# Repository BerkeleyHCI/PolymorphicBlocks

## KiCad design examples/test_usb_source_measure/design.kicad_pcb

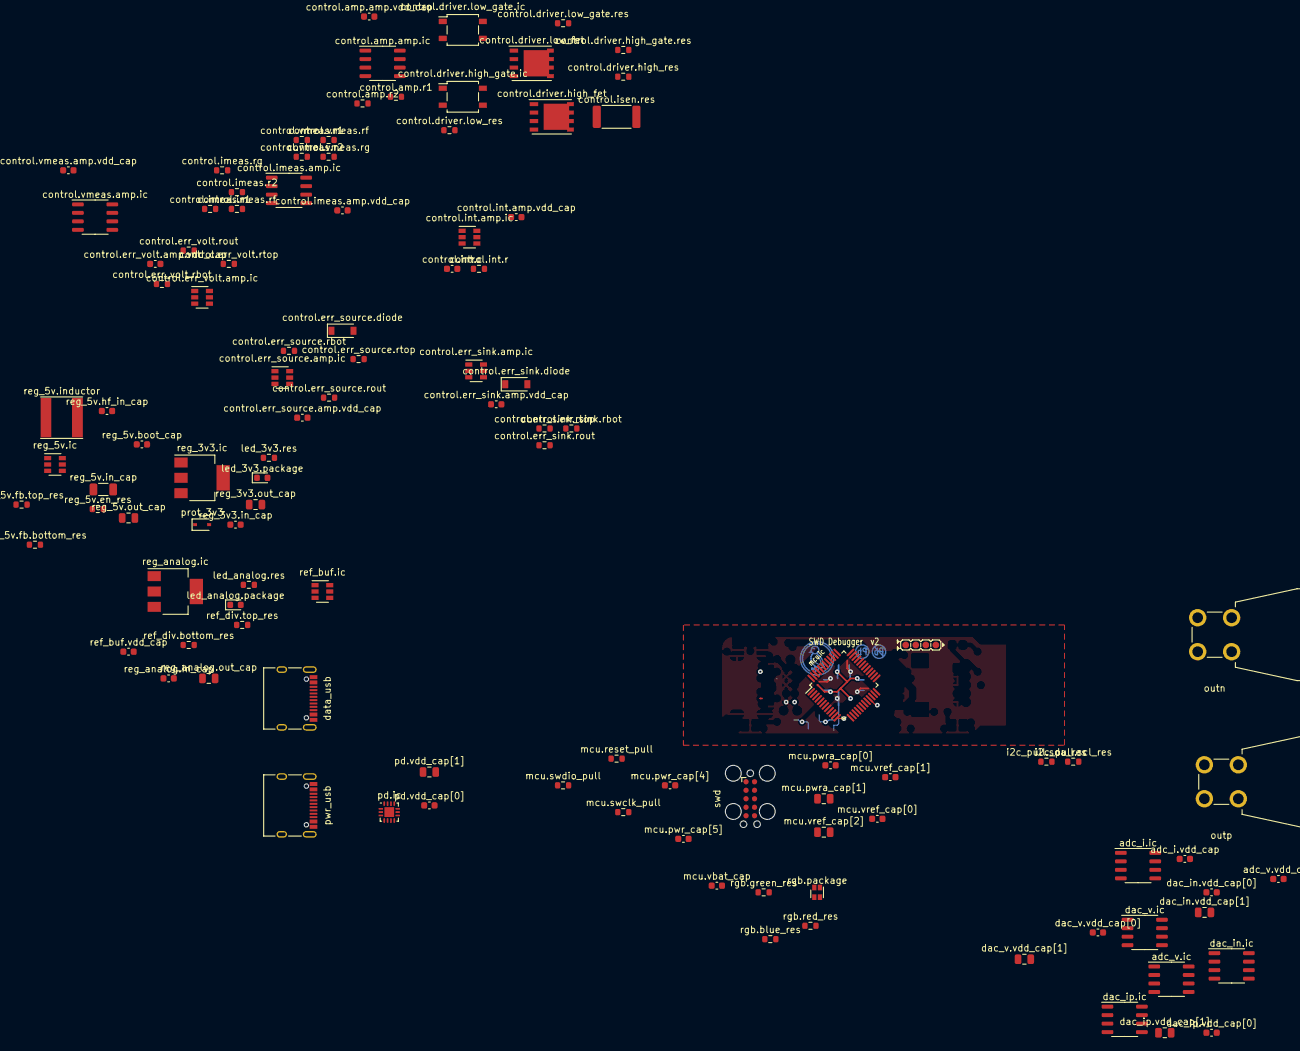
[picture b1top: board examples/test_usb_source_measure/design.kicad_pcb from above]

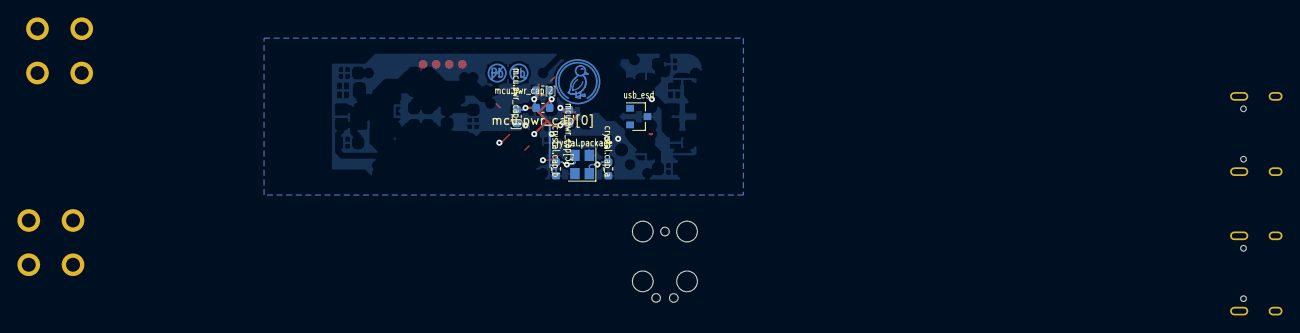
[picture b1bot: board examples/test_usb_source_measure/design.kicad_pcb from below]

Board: 4 copper layers, 120 parts (10 on the bottom side), 75 nets.

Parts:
adc_i.ic: MCP3201T-BI/SN (Microchip Technology); SO-8_3.9x4.9mm_P1.27mm
adc_i.vdd_cap: CL10A105KP8NNNC (Samsung Electro-Mechanics) - 1µF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; C_0603_1608Metric
adc_v.ic: MCP3201T-BI/SN (Microchip Technology); SO-8_3.9x4.9mm_P1.27mm
adc_v.vdd_cap: CL10A105KP8NNNC (Samsung Electro-Mechanics) - 1µF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; C_0603_1608Metric
control.amp.amp.ic, control.imeas.amp.ic, control.vmeas.amp.ic: OPA197IDR (Texas Instruments); SO-8_3.9x4.9mm_P1.27mm
control.amp.amp.vdd_cap, control.err_sink.amp.vdd_cap, control.err_source.amp.vdd_cap, control.err_volt.amp.vdd_cap, control.imeas.amp.vdd_cap, control.int.amp.vdd_cap, control.vmeas.amp.vdd_cap: CL10B104KB8NNNC (Samsung Electro-Mechanics) - 0.1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; C_0603_1608Metric
control.amp.r1: 39k, 1%, 0.1 W; R_0603_1608Metric
control.amp.r2: 2k, 1%, 0.1 W; R_0603_1608Metric
control.driver.high_fet: SIR172ADP-T1-GE3 (Vishay Siliconix) - Vds=30 V, I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; PowerPAK_SO-8_Single
control.driver.high_gate.ic, control.driver.low_gate.ic: G3VM-61GR2 (Omron Electronics); SO-4_4.4x4.3mm_P2.54mm
control.driver.high_gate.res, control.driver.low_gate.res: 220, 1%, 0.1 W; R_0603_1608Metric
control.driver.high_res, control.driver.low_res, control.err_sink.rout, control.err_source.rout, control.err_volt.rout, control.int.r: 4.7k, 1%, 0.1 W; R_0603_1608Metric
control.driver.low_fet: SQJ433EP-T1_GE3 (Vishay Siliconix) - Vds=30 V, Id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; PowerPAK_SO-8_Single
control.err_sink.amp.ic, control.err_source.amp.ic, control.err_volt.amp.ic, control.int.amp.ic: TLV9061SQDBVRQ1 (Texas Instruments); SOT-23-6
control.err_sink.diode, control.err_source.diode: DSS14UTR (SMC Diode Solutions) - Vr=40V, I=1A; D_SOD-123
control.err_sink.rbot, control.err_sink.rtop, control.err_source.rbot, control.err_source.rtop, control.err_volt.rbot, control.err_volt.rtop: 100k, 1%, 0.1 W; R_0603_1608Metric
control.imeas.r1, control.imeas.r2, control.imeas.rf, control.imeas.rg, control.vmeas.rf, control.vmeas.rg: 10k, 1%, 0.1 W; R_0603_1608Metric
control.int.c: CC0603GRNPO9BN102 (Yageo) - 1000pF, 50V; C_0603_1608Metric
control.isen.res: 100m, 1%, 1.0 W; R_2512_6332Metric
control.vmeas.r1, control.vmeas.r2: 220k, 1%, 0.1 W; R_0603_1608Metric
crystal.cap_a, crystal.cap_b: CL10C100JB8NNNC (Samsung Electro-Mechanics) - 10p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; C_0603_1608Metric
crystal.package: ABM8G-106-12.000MHZ-T (Abracon LLC) - 12MHz, 10pF; Oscillator_SMD_Abracon_ASE-4Pin_3.2x2.5mm
dac_in.ic: MCP4921-E/SN (Microchip Technology); SO-8_3.9x4.9mm_P1.27mm
dac_in.vdd_cap[0]: CL10B104KB8NNNC (Samsung Electro-Mechanics) - 0.1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; C_0603_1608Metric
dac_in.vdd_cap[1]: CL21A106KPFNNNE (Samsung Electro-Mechanics) - 10µ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; C_0805_2012Metric
dac_ip.ic: MCP4921-E/SN (Microchip Technology); SO-8_3.9x4.9mm_P1.27mm
dac_ip.vdd_cap[0]: CL10B104KB8NNNC (Samsung Electro-Mechanics) - 0.1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; C_0603_1608Metric
dac_ip.vdd_cap[1]: CL21A106KPFNNNE (Samsung Electro-Mechanics) - 10µ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; C_0805_2012Metric
dac_v.ic: MCP4921-E/SN (Microchip Technology); SO-8_3.9x4.9mm_P1.27mm
dac_v.vdd_cap[0]: CL10B104KB8NNNC (Samsung Electro-Mechanics) - 0.1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; C_0603_1608Metric
dac_v.vdd_cap[1]: CL21A106KPFNNNE (Samsung Electro-Mechanics) - 10µ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; C_0805_2012Metric
data_usb: COM-15111 (Sparkfun); USB_C_Receptacle_XKB_U262-16XN-4BVC11
duck: Duck; Symbol_Duckling
i2c_pull.scl_res, i2c_pull.sda_res: 4.7k, 1%, 0.1 W; R_0603_1608Metric
id: IdDots4; Indicator_IdDots_4
leadfree: LeadFree; Indicator_LeadFree
led_3v3.package: LED; LED_0603_1608Metric
led_3v3.res: 1k, 1%, 0.1 W; R_0603_1608Metric
led_analog.package: LED; LED_0603_1608Metric
led_analog.res: 1k, 1%, 0.1 W; R_0603_1608Metric
mcu.ic: LPC1549JBD48 (NXP); LQFP-48_7x7mm_P0.5mm
mcu.pwr_cap[0], mcu.pwr_cap[2], mcu.pwr_cap[4], mcu.pwra_cap[0], mcu.vbat_cap, mcu.vref_cap[0], mcu.vref_cap[1]: CL10B104KB8NNNC (Samsung Electro-Mechanics) - 0.1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; C_0603_1608Metric
mcu.pwr_cap[1], mcu.pwr_cap[3], mcu.pwr_cap[5]: CL10B103KB8NNNC (Samsung Electro-Mechanics) - 100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; C_0603_1608Metric
mcu.pwra_cap[1], mcu.vref_cap[2]: CL21A106KPFNNNE (Samsung Electro-Mechanics) - 10µ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; C_0805_2012Metric
mcu.reset_pull, mcu.swclk_pull, mcu.swdio_pull: 10k, 1%, 0.1 W; R_0603_1608Metric
outn: CT3151-* (CalTest); CalTest_CT3151
outp: CT3151-* (CalTest); CalTest_CT3151
pd.ic: FUSB302B11MPX (ON Semiconductor); WQFN-14-1EP_2.5x2.5mm_P0.5mm_EP1.45x1.45mm
pd.vdd_cap[0]: CL10B104KB8NNNC (Samsung Electro-Mechanics) - 0.1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; C_0603_1608Metric
pd.vdd_cap[1]: CL21A106KPFNNNE (Samsung Electro-Mechanics) - 10µ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; C_0805_2012Metric
prot_3v3: DDZ3V6ASF-7 (Diodes Incorporated) - Vz=3.57V, I=9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; D_SOD-323
pwr_usb: COM-15111 (Sparkfun); USB_C_Receptacle_XKB_U262-16XN-4BVC11
ref_buf.ic: TLV9061SQDBVRQ1 (Texas Instruments); SOT-23-6
ref_buf.vdd_cap: CL10B104KB8NNNC (Samsung Electro-Mechanics) - 0.1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; C_0603_1608Metric
ref_div.bottom_res, ref_div.top_res: 100k, 1%, 0.1 W; R_0603_1608Metric
reg_3v3.ic: LD1117S33TR (STMicroelectronics); SOT-223-3_TabPin2
reg_3v3.in_cap, reg_5v.boot_cap, reg_5v.hf_in_cap: CL10B104KB8NNNC (Samsung Electro-Mechanics) - 0.1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; C_0603_1608Metric
reg_3v3.out_cap, reg_5v.out_cap: CL21A106KPFNNNE (Samsung Electro-Mechanics) - 10µ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; C_0805_2012Metric
reg_5v.en_res: 510k, 1%, 0.1 W; R_0603_1608Metric
reg_5v.fb.bottom_res: 1.5k, 1%, 0.1 W; R_0603_1608Metric
reg_5v.fb.top_res: 11k, 1%, 0.1 W; R_0603_1608Metric
reg_5v.ic: TPS54202H (Texas Instruments); SOT-23-6
reg_5v.in_cap: CL31A226KAHNNNE (Samsung Electro-Mechanics) - 22µ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; C_1206_3216Metric
reg_5v.inductor: NR6028T470M (Taiyo Yuden) - 47µH, 920mA; L_Taiyo-Yuden_NR-60xx
reg_analog.ic: LD1117S25TR (STMicroelectronics); SOT-223-3_TabPin2
reg_analog.in_cap: CL10B104KB8NNNC (Samsung Electro-Mechanics) - 0.1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; C_0603_1608Metric
reg_analog.out_cap: CL21A106KPFNNNE (Samsung Electro-Mechanics) - 10µ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; C_0805_2012Metric
rgb.blue_res, rgb.green_res, rgb.red_res: 1k, 1%, 0.1 W; R_0603_1608Metric
rgb.package: EAST1616RGBB2 (Everlight Electronics Co Ltd); LED_LiteOn_LTST-C19HE1WT
swd: SWD; Tag-Connect_TC2050-IDC-FP_2x05_P1.27mm_Vertical
usb_esd: TPD2E009 (Texas Instruments); SOT-23

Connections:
(adapter)outp.port.src: control.imeas.r1.1, control.isen.res.2, control.vmeas.r2.1, outp.1
adc_i.vin: adc_i.ic.2, control.err_sink.rbot.1, control.err_source.rbot.1, control.imeas.amp.ic.6, control.imeas.rf.1
adc_v.cs: adc_v.ic.5, mcu.ic.48
adc_v.spi.mosi: dac_in.ic.4, dac_ip.ic.4, dac_v.ic.4, mcu.ic.46
control.amp.(adapter)r1.b.src: control.amp.amp.ic.2, control.amp.r1.2, control.amp.r2.1
control.amp.input: control.amp.amp.ic.3, control.int.amp.ic.1, control.int.c.1
control.control_current_source: control.err_source.rtop.1, dac_ip.ic.8
control.control_voltage: control.err_volt.rtop.1, dac_v.ic.8
control.driver.(adapter)high_res.b.src: control.driver.high_gate.ic.4, control.driver.high_res.1, control.driver.high_res.2
control.driver.control: control.amp.amp.ic.6, control.amp.r1.1, control.driver.high_gate.ic.3, control.driver.low_gate.ic.3
control.driver.high_gate.ic.ledk: control.driver.high_gate.ic.2, control.driver.high_gate.res.1
control.driver.low_gate.ic.ledk: control.driver.low_gate.ic.2, control.driver.low_gate.res.1
control.driver.low_res.a: control.driver.low_gate.ic.4, control.driver.low_res.1, control.driver.low_res.2
control.err_sink.(adapter)diode.cathode.src: control.err_sink.amp.ic.1, control.err_sink.diode.1
control.err_sink.diode.anode: control.err_sink.diode.2, control.err_sink.rout.1
control.err_sink.rtop.b: control.err_sink.amp.ic.3, control.err_sink.rbot.2, control.err_sink.rtop.2
control.err_source.(adapter)diode.anode.dst: control.err_source.amp.ic.1, control.err_source.diode.2
control.err_source.(adapter)rbot.b.dst: control.err_source.amp.ic.3, control.err_source.rbot.2, control.err_source.rtop.2
control.err_source.(adapter)rout.a.dst: control.err_source.diode.1, control.err_source.rout.1
control.err_volt.(adapter)rbot.b.dst: control.err_volt.amp.ic.3, control.err_volt.rbot.2, control.err_volt.rtop.2
control.err_volt.rout.a: control.err_volt.amp.ic.1, control.err_volt.rout.1
control.imeas.(adapter)rf.b.src: control.imeas.amp.ic.2, control.imeas.r1.2, control.imeas.rf.2
control.imeas.amp.inp: control.imeas.amp.ic.3, control.imeas.r2.2, control.imeas.rg.2
control.imeas.input_positive: control.driver.high_fet.1, control.driver.high_fet.2, control.driver.high_fet.3, control.driver.high_fet.4, control.driver.low_fet.1, control.driver.low_fet.2, control.driver.low_fet.3, control.driver.low_fet.4, control.imeas.r2.1, control.isen.res.1
control.int.(adapter)r.b.dst: control.int.amp.ic.4, control.int.c.2, control.int.r.2
control.int_link: control.err_sink.amp.ic.4, control.err_sink.rout.2, control.err_source.amp.ic.4, control.err_source.rout.2, control.err_volt.amp.ic.4, control.err_volt.rout.2, control.int.r.1
control.low_en: control.driver.low_gate.ic.1, mcu.ic.28
control.measured_voltage: adc_v.ic.2, control.err_volt.rbot.1, control.vmeas.amp.ic.6, control.vmeas.rf.1
control.vmeas.(adapter)rf.b.src: control.vmeas.amp.ic.2, control.vmeas.r1.2, control.vmeas.rf.2
control.vmeas.rg.b: control.vmeas.amp.ic.3, control.vmeas.r2.2, control.vmeas.rg.2
crystal.crystal.b: crystal.cap_b.1, crystal.package.3, mcu.ic.25
dac_in.out: control.err_sink.rtop.1, dac_in.ic.8
dac_in.spi.miso: adc_i.ic.6, adc_v.ic.6, mcu.ic.1
dac_in.spi.sck: adc_i.ic.7, adc_v.ic.7, dac_in.ic.3, dac_ip.ic.3, dac_v.ic.3, mcu.ic.12
dac_ip.ldac: dac_in.ic.5, dac_ip.ic.5, dac_v.ic.5, mcu.ic.44
dac_v.cs: dac_v.ic.2, mcu.ic.43
data_usb.B4: data_usb.A4, data_usb.A9, data_usb.B4, data_usb.B9
data_usb.usb.dm: data_usb.A7, data_usb.B7, mcu.ic.36, usb_esd.1
gnd: adc_i.ic.3, adc_i.ic.4, adc_i.vdd_cap.2, adc_v.ic.3, adc_v.ic.4, adc_v.vdd_cap.2, control.amp.amp.ic.4, control.amp.amp.vdd_cap.2, control.driver.high_gate.res.2, control.driver.low_fet.5, control.driver.low_gate.res.2, control.err_sink.amp.ic.2, control.err_sink.amp.vdd_cap.2, control.err_source.amp.ic.2, control.err_source.amp.vdd_cap.2, control.err_volt.amp.ic.2, control.err_volt.amp.vdd_cap.2, control.imeas.amp.ic.4, control.imeas.amp.vdd_cap.2, control.int.amp.ic.2, control.int.amp.vdd_cap.2, control.vmeas.amp.ic.4, control.vmeas.amp.vdd_cap.2, control.vmeas.r1.1, crystal.cap_a.2, crystal.cap_b.2, crystal.package.2, crystal.package.4, dac_in.ic.7, dac_in.vdd_cap[0].2, dac_in.vdd_cap[1].2, dac_ip.ic.7, dac_ip.vdd_cap[0].2, dac_ip.vdd_cap[1].2, dac_v.ic.7, dac_v.vdd_cap[0].2, dac_v.vdd_cap[1].2, data_usb.A1, data_usb.A12, data_usb.B1, data_usb.B12, led_3v3.res.2, led_analog.res.2, mcu.ic.11, mcu.ic.17, mcu.ic.20, mcu.ic.40, mcu.ic.41, mcu.pwr_cap[0].2, mcu.pwr_cap[1].2, mcu.pwr_cap[2].2, mcu.pwr_cap[3].2, mcu.pwr_cap[4].2, mcu.pwr_cap[5].2, mcu.pwra_cap[0].2, mcu.pwra_cap[1].2, mcu.swclk_pull.1, mcu.vbat_cap.2, mcu.vref_cap[0].2, mcu.vref_cap[1].2, mcu.vref_cap[2].2, outn.1, pd.ic.8, pd.ic.9, pd.ic.15, pd.vdd_cap[0].2, pd.vdd_cap[1].2, prot_3v3.2, pwr_usb.A1, pwr_usb.A12, pwr_usb.B1, pwr_usb.B12, ref_buf.ic.2, ref_buf.vdd_cap.2, ref_div.bottom_res.2, reg_3v3.ic.1, reg_3v3.in_cap.2, reg_3v3.out_cap.2, reg_5v.fb.bottom_res.2, reg_5v.hf_in_cap.2, reg_5v.ic.1, reg_5v.in_cap.2, reg_5v.out_cap.2, reg_analog.ic.1, reg_analog.in_cap.2, reg_analog.out_cap.2, swd.2, swd.3, swd.5, usb_esd.3
led_3v3.res.a: led_3v3.package.1, led_3v3.res.1
led_analog.package.k: led_analog.package.1, led_analog.res.1
mcu.digital[1]: mcu.ic.8, rgb.red_res.2
mcu.digital[5]: dac_ip.ic.2, mcu.ic.47
mcu.digital[6]: dac_in.ic.2, mcu.ic.2
mcu.digital[8]: adc_i.ic.5, mcu.ic.4
mcu.digital[10]: control.driver.high_gate.ic.1, mcu.ic.3
mcu.i2c_0.scl: i2c_pull.scl_res.2, pd.ic.6
mcu.swd.swclk: mcu.ic.29, mcu.swclk_pull.2, swd.9
mcu.swd.swo: mcu.ic.9, swd.8
mcu.xtal.xtal_in: crystal.cap_a.1, crystal.package.1, mcu.ic.26
pd.i2c.sda: i2c_pull.sda_res.2, pd.ic.7
pd.ic.vconn: pd.ic.12, pd.ic.13
pd.int: mcu.ic.22, pd.ic.5
pwr_usb.cc.cc1: pd.ic.10, pd.ic.11, pwr_usb.A5
pwr_usb.cc.cc2: pd.ic.1, pd.ic.14, pwr_usb.B5
pwr_usb.usb.dm: pwr_usb.A7, pwr_usb.B7
pwr_usb.usb.dp: pwr_usb.A6, pwr_usb.B6
ref_buf.inp: ref_buf.ic.3, ref_div.bottom_res.1, ref_div.top_res.2
ref_buf.output: control.amp.r2.2, control.imeas.rg.1, control.int.amp.ic.3, control.vmeas.rg.1, ref_buf.ic.1, ref_buf.ic.4
reg_5v.(adapter)en_res.b.dst: reg_5v.en_res.2, reg_5v.ic.5
reg_5v._pwr_out_net: reg_3v3.ic.3, reg_3v3.in_cap.1, reg_5v.fb.top_res.1, reg_5v.inductor.2, reg_5v.out_cap.1, reg_analog.ic.3, reg_analog.in_cap.1
reg_5v._switch_net: reg_5v.boot_cap.2, reg_5v.ic.2, reg_5v.inductor.1
reg_5v.boot_cap.pos: reg_5v.boot_cap.1, reg_5v.ic.6
reg_5v.fb.output: reg_5v.fb.bottom_res.1, reg_5v.fb.top_res.2, reg_5v.ic.4
rgb.blue: mcu.ic.45, rgb.blue_res.2
rgb.blue_res.a: rgb.blue_res.1, rgb.package.1
rgb.green: mcu.ic.21, rgb.green_res.2
rgb.package.k_green: rgb.green_res.1, rgb.package.4
rgb.package.k_red: rgb.package.3, rgb.red_res.1
swd.swd.reset: mcu.ic.34, mcu.reset_pull.2, swd.6
swd.swd.swdio: mcu.ic.33, mcu.swdio_pull.2, swd.10
usb_esd.usb.dp: data_usb.A6, data_usb.B6, mcu.ic.35, usb_esd.2
v3v3: adc_i.ic.8, adc_i.vdd_cap.1, adc_v.ic.8, adc_v.vdd_cap.1, control.err_sink.amp.ic.5, control.err_sink.amp.ic.6, control.err_sink.amp.vdd_cap.1, control.err_source.amp.ic.5, control.err_source.amp.ic.6, control.err_source.amp.vdd_cap.1, control.err_volt.amp.ic.5, control.err_volt.amp.ic.6, control.err_volt.amp.vdd_cap.1, control.int.amp.ic.5, control.int.amp.ic.6, control.int.amp.vdd_cap.1, dac_in.ic.1, dac_in.vdd_cap[0].1, dac_in.vdd_cap[1].1, dac_ip.ic.1, dac_ip.vdd_cap[0].1, dac_ip.vdd_cap[1].1, dac_v.ic.1, dac_v.vdd_cap[0].1, dac_v.vdd_cap[1].1, i2c_pull.scl_res.1, i2c_pull.sda_res.1, led_3v3.package.2, mcu.ic.10, mcu.ic.14, mcu.ic.16, mcu.ic.27, mcu.ic.30, mcu.ic.39, mcu.ic.42, mcu.pwr_cap[0].1, mcu.pwr_cap[1].1, mcu.pwr_cap[2].1, mcu.pwr_cap[3].1, mcu.pwr_cap[4].1, mcu.pwr_cap[5].1, mcu.pwra_cap[0].1, mcu.pwra_cap[1].1, mcu.reset_pull.1, mcu.swdio_pull.1, mcu.vbat_cap.1, mcu.vref_cap[0].1, mcu.vref_cap[1].1, mcu.vref_cap[2].1, pd.ic.3, pd.ic.4, pd.vdd_cap[0].1, pd.vdd_cap[1].1, prot_3v3.1, reg_3v3.ic.2, reg_3v3.out_cap.1, rgb.package.2, swd.1
vref: adc_i.ic.1, adc_v.ic.1, dac_in.ic.6, dac_ip.ic.6, dac_v.ic.6, led_analog.package.2, ref_buf.ic.5, ref_buf.ic.6, ref_buf.vdd_cap.1, ref_div.top_res.1, reg_analog.ic.2, reg_analog.out_cap.1
vusb: control.amp.amp.ic.7, control.amp.amp.vdd_cap.1, control.driver.high_fet.5, control.imeas.amp.ic.7, control.imeas.amp.vdd_cap.1, control.vmeas.amp.ic.7, control.vmeas.amp.vdd_cap.1, pd.ic.2, pwr_usb.A4, pwr_usb.A9, pwr_usb.B4, pwr_usb.B9, reg_5v.en_res.1, reg_5v.hf_in_cap.1, reg_5v.ic.3, reg_5v.in_cap.1

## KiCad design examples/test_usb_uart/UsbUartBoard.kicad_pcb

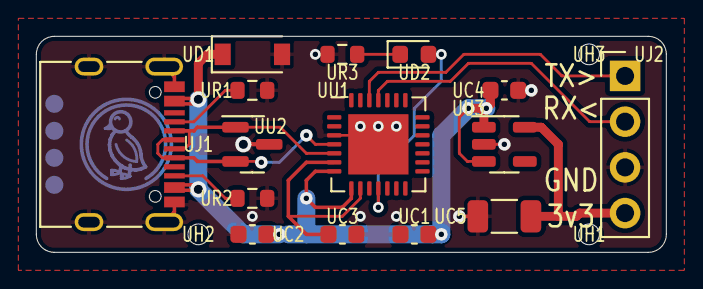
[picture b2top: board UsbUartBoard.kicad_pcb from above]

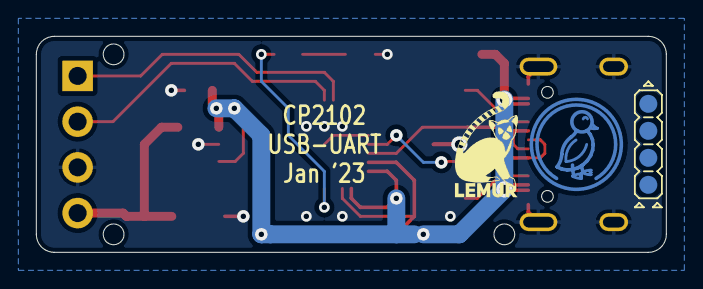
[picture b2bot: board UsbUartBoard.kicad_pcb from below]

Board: 2 copper layers, 35.0 x 12.0 mm, 21 parts (3 on the bottom side), 12 nets.

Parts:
UC1, UC2, UC3, UC4: C_0603_1608Metric
UC5: C_1206_3216Metric
UD1: MMSZ5232A_R1_00001 (PANJIT International) - 5?A@3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; D_SOD-123
UD2: C2290 (Hubei KENTO Elec) - White 0603 Light Emitt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; LED_0603_1608Metric
UH1, UH2, UH3: JlcToolingHole_1.152mm
UJ1: COM-15111 (Sparkfun); USB_C_Receptacle_XKB_U262-16XN-4BVC11
UJ2: PinHeader2.54 1x4 (Generic); PinHeader_1x04_P2.54mm_Vertical
UR1, UR2, UR3: R_0603_1608Metric
UU1: CP2102 (Silicon Labs); QFN-28-1EP_5x5mm_P0.5mm_EP3.35x3.35mm
UU2: PGB102ST23 (Littelfuse); SOT-23
UU3: AP2204K-3.3 (Diodes Incorporated); SOT-23-5
UU4: Duck; Symbol_Duckling
UU5: Lemur; Symbol_LemurSmall
UU6: IdDots4; Indicator_IdDots_4

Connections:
gnd: UC1.2, UC2.2, UC3.2, UC4.2, UC5.2, UD1.2, UJ1.A1, UJ1.A12, UJ1.B1, UJ1.B12, UJ1.S1, UJ2.3, UR1.1, UR2.1, UR3.2, UU1.3, UU1.29, UU2.3, UU3.2
led.res.a: UD2.1, UR3.1
usb_chain_0.d_N: UJ1.A7, UJ1.B7, UU1.5, UU2.1
usb_chain_0.d_P: UJ1.A6, UJ1.B6, UU1.4, UU2.2
usb_uart.conn.A5: UJ1.A5, UR1.2
usb_uart.conn.B5: UJ1.B5, UR2.2
usbconv.ic.vdd: UC3.1, UU1.6, UU1.9
usbconv.nsuspend: UD2.2, UU1.11
usbconv.uart.rx: UJ2.2, UU1.25
usbconv.uart.tx: UJ2.1, UU1.26
v3v3: UC5.1, UJ2.4, UU3.5
vusb: UC1.1, UC2.1, UC4.1, UD1.1, UJ1.A4, UJ1.A9, UJ1.B4, UJ1.B9, UU1.7, UU1.8, UU3.1, UU3.3

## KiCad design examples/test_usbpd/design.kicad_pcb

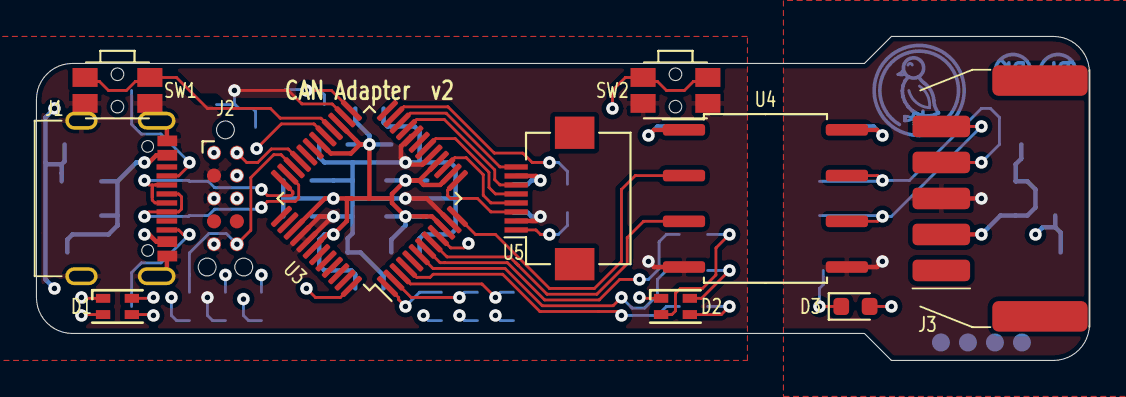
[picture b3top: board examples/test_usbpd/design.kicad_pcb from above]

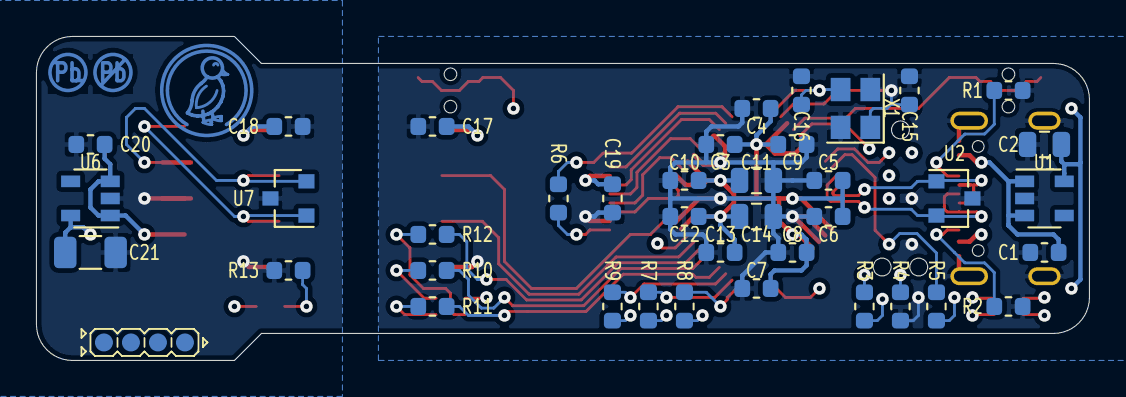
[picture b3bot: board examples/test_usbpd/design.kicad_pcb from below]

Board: 4 copper layers, 58.5 x 18.0 mm, 53 parts (42 on the bottom side), 42 nets.

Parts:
1: LeadFree; Indicator_LeadFree
2: IdDots4; Indicator_IdDots_4
C1, C19: CL10A105KP8NNNC (Samsung Electro-Mechanics) - 1µF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; C_0603_1608Metric
C2: CL21B225KPFNNNE (Samsung Electro-Mechanics) - 2.2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; C_0805_2012Metric
C3, C5, C7, C9, C10, C12, C13, C17, C18: CL10B104KB8NNNC (Samsung Electro-Mechanics) - 0.1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; C_0603_1608Metric
C4, C6, C8: CL10B103KB8NNNC (Samsung Electro-Mechanics) - 100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; C_0603_1608Metric
C11, C14: CL21A106KPFNNNE (Samsung Electro-Mechanics) - 10µ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; C_0805_2012Metric
C15, C16: CC0603GRNPO9BN180 (Yageo) - 18pF, 50V; C_0603_1608Metric
C20: CL10A105KA8NNNC (Samsung Electro-Mechanics) - 1µF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; C_0603_1608Metric
C21: CL31B225KOHNNNE (Samsung Electro-Mechanics) - 2.2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; C_1206_3216Metric
D1, D2: EAST1616RGBB2 (Everlight Electronics Co Ltd); LED_RGB_0606
D3: LED; LED_0603_1608Metric
J1: COM-15111 (Sparkfun); USB_C_Receptacle_BSC_A40-00119
J2: SWD; Tag-Connect_TC2050-IDC-NL_2x05_P1.27mm_Vertical
J3: 5023520500 (Molex); Molex_DuraClik_502352_1x05_P2.00mm_Horizontal
R1, R2: 5.1k, 1%, 0.1W; R_0603_1608Metric
R3, R4, R5: 10k, 1%, 0.1W; R_0603_1608Metric
R6: 100, 1%, 0.1W; R_0603_1608Metric
R7, R8, R9, R10, R11, R12, R13: 1k, 1%, 0.1W; R_0603_1608Metric
SW1, SW2: EVQ-P7C01P; SW_SPST_EVQP7C
U1: AP2204K-3.3 (Diodes Incorporated); SOT-23-5
U2: TPD2E009 (Texas Instruments); SOT-23
U3: LPC1549JBD48 (NXP); LQFP-48_7x7mm_P0.5mm
U4: ISO1050DUB (Texas Instruments); SOP-8_6.62x9.15mm_P2.54mm
U5: QT096T_IF09, FH12-8S-0.5SH(55); Hirose_FH12-8S-0.5SH_1x08-1MP_P0.50mm_Horizontal
U6: AP2204K-5.0 (Diodes Incorporated); SOT-23-5
U7: PESD1CAN,215; SOT-23
U8: Duck; Symbol_Duckling
X1: 7V-12.000MAHE-T (TXC); Oscillator_SMD_Abracon_ASE-4Pin_3.2x2.5mm

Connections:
can.differential.canl: J3.5, U4.6, U7.1
can_esd.can.canh: J3.4, U4.7, U7.2
can_gnd: C18.2, C20.2, C21.2, J3.3, R13.2, U4.5, U6.2, U7.3
can_reg.pwr_out: C18.1, C21.1, D3.2, U4.8, U6.5
can_vcan: C20.1, J3.2, U6.1, U6.3
crystal.crystal.a: C15.1, U3.26, X1.1
crystal.crystal.b: C16.1, U3.25, X1.3
gnd: C1.2, C2.2, C3.2, C4.2, C5.2, C6.2, C7.2, C8.2, C9.2, C10.2, C11.2, C12.2, C13.2, C14.2, C15.2, C16.2, C17.2, C19.2, J1.A1B12, J1.B1A12, J1.S, J2.2, J2.3, J2.5, R1.1, R2.1, R4.1, SW1.1, SW2.1, U1.2, U2.3, U3.11, U3.17, U3.20, U3.40, U3.41, U4.4, U5.2, X1.2, X1.4
lcd.led: R6.1, U3.23
lcd.led_res.b: R6.2, U5.1
led_can.res.a: D3.1, R13.1
mcu.can_0.rxd: U3.12, U4.2
mcu.can_0.txd: U3.8, U4.3
mcu.digital_12: R10.2, U3.6
mcu.digital_13: R9.2, U3.3
mcu.digital_15: R7.2, U3.2
mcu.digital_16: U3.22, U5.8
mcu.digital_17: U3.15, U5.4
mcu.digital_18: U3.13, U5.3
mcu.spi_1.mosi: U3.18, U5.5
mcu.spi_1.sck: U3.21, U5.6
mcu.swd.reset: J2.6, R5.2, U3.34
mcu.swd.swclk: J2.9, R4.2, U3.29
mcu.swd.swdio: J2.10, R3.2, U3.33
mcu.swd.swo: J2.8, U3.9
rgb_can.blue: R12.2, U3.7
rgb_can.blue_res.a: D2.2, R12.1
rgb_can.green: R11.2, U3.4
rgb_can.package.green_k: D2.3, R11.1
rgb_can.red_res.a: D2.4, R10.1
rgb_usb.green: R8.2, U3.1
rgb_usb.package.blue_k: D1.2, R9.1
rgb_usb.package.green_k: D1.3, R8.1
rgb_usb.package.red_k: D1.4, R7.1
sw_can.out: SW2.2, U3.48
sw_usb.a: SW1.2, U3.28
usb.port.A5: J1.A5, R1.2
usb.port.B5: J1.B5, R2.2
usb_net.d_N: J1.A7, J1.B7, U2.1, U3.36
usb_net.d_P: J1.A6, J1.B6, U2.2, U3.35
v3v3: C2.1, C3.1, C4.1, C5.1, C6.1, C7.1, C8.1, C9.1, C10.1, C11.1, C12.1, C13.1, C14.1, C17.1, C19.1, D1.1, D2.1, J2.1, R3.1, R5.1, U1.5, U3.10, U3.14, U3.16, U3.27, U3.30, U3.39, U3.42, U4.1, U5.7
vusb: C1.1, J1.A4B9, J1.B4A9, U1.1, U1.3
